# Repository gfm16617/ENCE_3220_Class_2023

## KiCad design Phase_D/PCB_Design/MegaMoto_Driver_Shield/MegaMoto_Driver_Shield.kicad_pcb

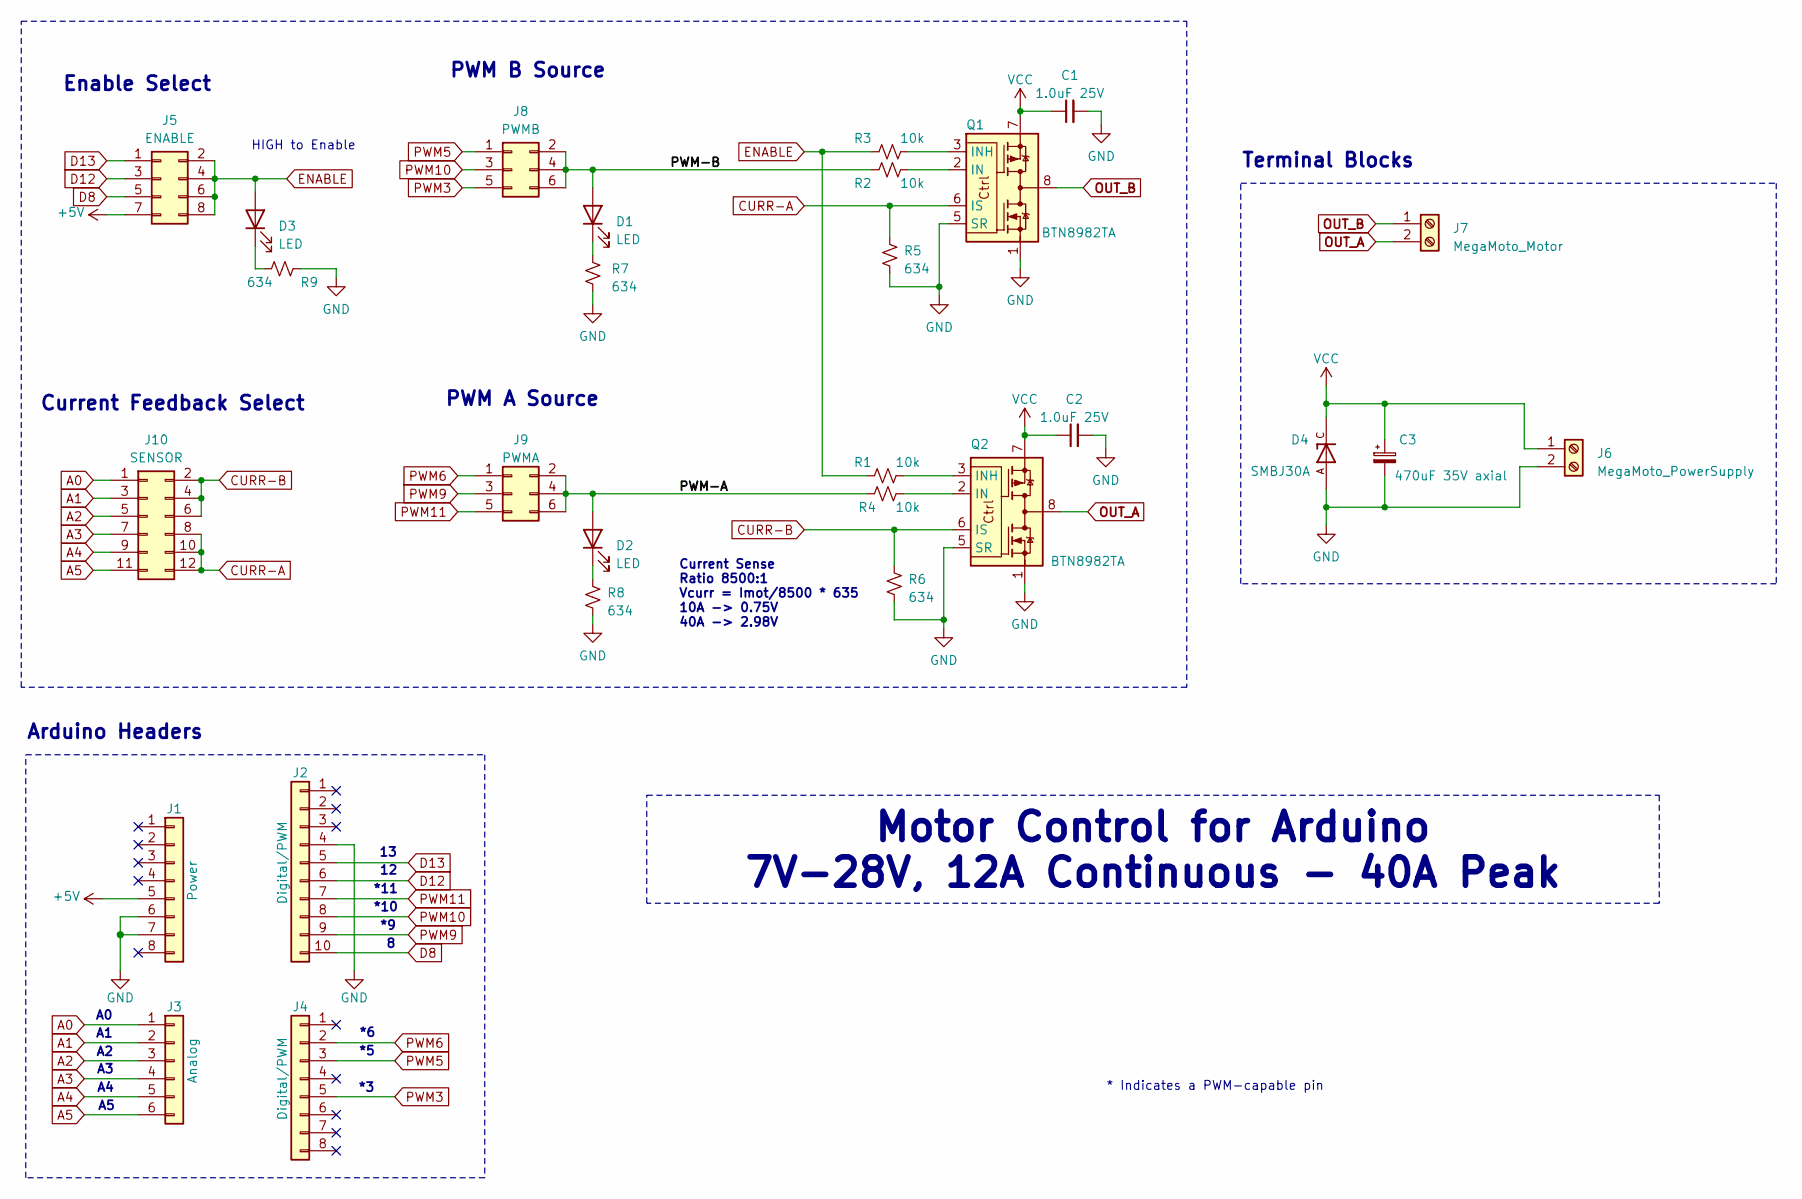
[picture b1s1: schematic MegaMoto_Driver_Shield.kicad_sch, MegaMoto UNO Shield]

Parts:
C1, C2: 1.0uF 25V; C_0603_1608Metric
C3: 470uF 35V axial; CP_Axial_L20.0mm_D10.0mm_P26.00mm_Horizontal
D1, D2, D3: LED; LED_0805_2012Metric
D4: SMBJ30A; DIOM4336X265N; PARTREV F2102
J1: Power; PinSocket_1x08_P2.54mm_Vertical
J2: Digital/PWM; PinSocket_1x10_P2.54mm_Vertical
J3: Analog; PinSocket_1x06_P2.54mm_Vertical
J4: Digital/PWM; PinSocket_1x08_P2.54mm_Vertical
J5: ENABLE; PinHeader_2x04_P2.54mm_Vertical
J6: MegaMoto_PowerSupply; Term_Block_1x2_P5mm
J7: MegaMoto_Motor; Term_Block_1x2_P5mm
J8: PWMB; PinHeader_2x03_P2.54mm_Vertical
J9: PWMA; PinHeader_2x03_P2.54mm_Vertical
J10: SENSOR; PinHeader_2x06_P2.54mm_Vertical
Q1, Q2: BTN8982TA; TO-263-7_TabPin8
R1, R2, R3, R4: 10k; R_0603_1608Metric
R5, R6, R7, R8, R9: 634; R_0603_1608Metric

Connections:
+5V: J1.5, J5.7
/PWM-A: D2.2 (A), J9.2, J9.4, J9.6, R4.1
/PWM-B: D1.2 (A), J8.2, J8.4, J8.6, R2.1
A0: J3.1, J10.1
A1: J3.2, J10.3
A2: J3.3, J10.5
A3: J3.4, J10.7
A4: J3.5, J10.9
A5: J3.6, J10.11
CURR-A: J10.8, J10.10, J10.12, Q1.6 (IS), R5.1
CURR-B: J10.2, J10.4, J10.6, Q2.6 (IS), R6.1
D8: J2.10, J5.5
D12: J2.6, J5.3
D13: J2.5, J5.1
ENABLE: D3.2 (A), J5.2, J5.4, J5.6, J5.8, R1.1, R3.1
GND: C1.2, C2.2, C3.2, D4.A, J1.6, J1.7, J2.4, J6.2, Q1.1, Q1.5 (SR), Q2.1, Q2.5 (SR), R5.2, R6.2, R7.2, R8.2, R9.2
unnamed: D1.1 (K), R7.1
unnamed: D2.1 (K), R8.1
unnamed: D3.1 (K), R9.1
unnamed: Q1.2 (IN), R2.2
unnamed: Q1.3 (INH), R3.2
unnamed: Q2.2 (IN), R4.2
unnamed: Q2.3 (INH), R1.2
OUT_A: J7.2, Q2.4, Q2.8
OUT_B: J7.1, Q1.4, Q1.8
PWM3: J4.5, J8.5
PWM5: J4.3, J8.1
PWM6: J4.2, J9.1
PWM9: J2.9, J9.3
PWM10: J2.8, J8.3
PWM11: J2.7, J9.5
VCC: C1.1, C2.1, C3.1, D4.C, J6.1, Q1.7, Q2.7

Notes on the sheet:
Motor Control for Arduino 7V-28V, 12A Continuous - 40A Peak
Terminal Blocks
Current Sense Ratio 8500:1 Vcurr = Imot/8500 * 635 10A -> 0.75V 40A -> 2.98V
*11
HIGH to Enable
Current Feedback Select
Enable Select
PWM A Source
*10
PWM B Source
* Indicates a PWM-capable pin
Arduino Headers

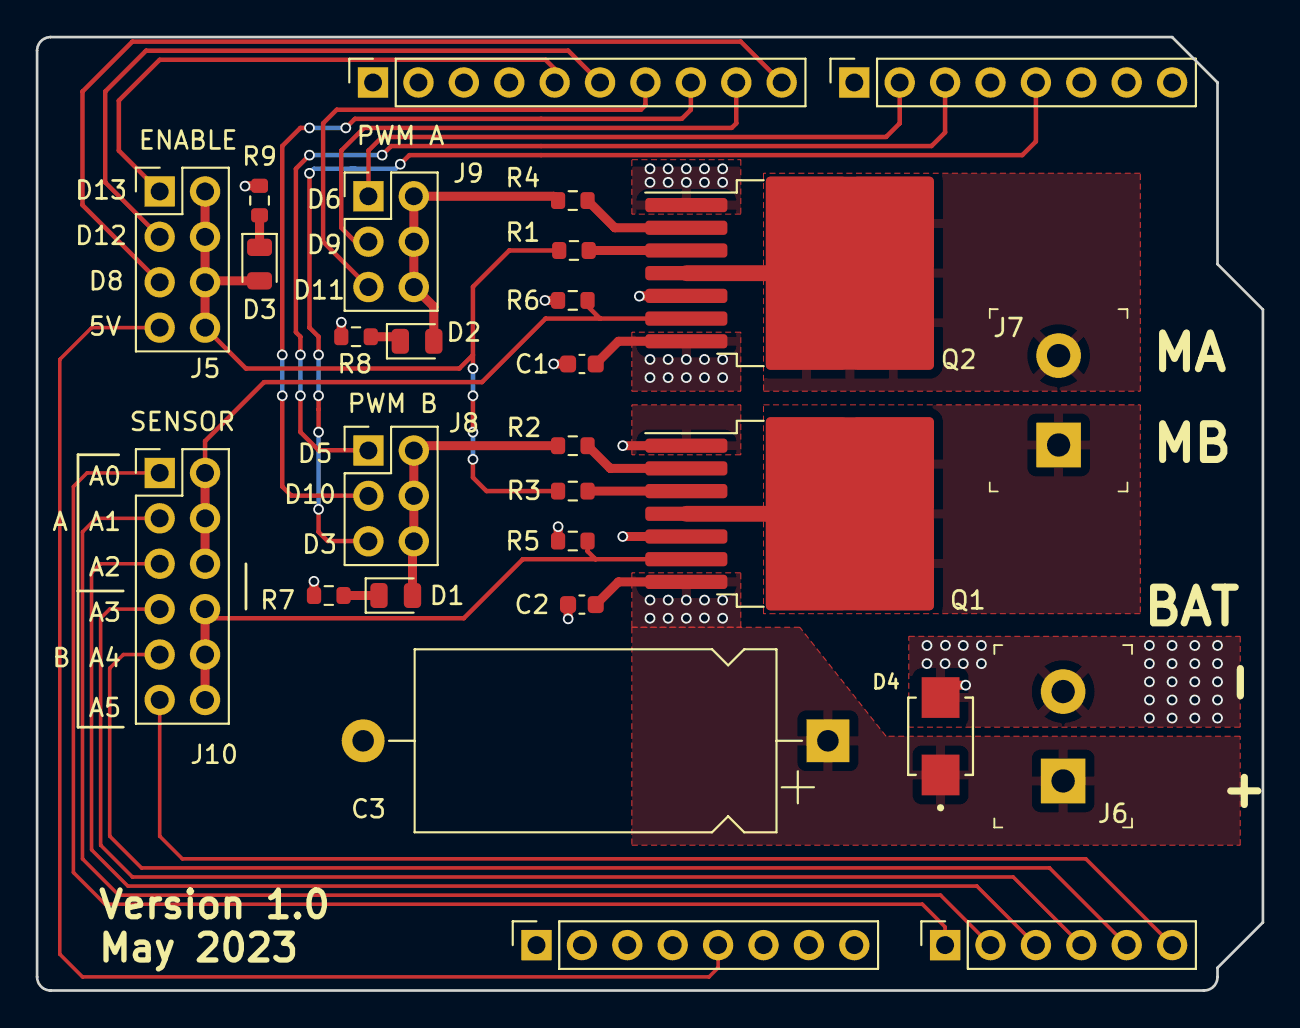
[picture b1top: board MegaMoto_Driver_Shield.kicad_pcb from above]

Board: 2 copper layers, 68.6 x 53.3 mm, 28 parts (0 on the bottom side), 32 nets.

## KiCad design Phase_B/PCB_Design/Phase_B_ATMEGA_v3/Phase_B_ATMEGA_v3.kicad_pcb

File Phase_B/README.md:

## Table of Contents
- [PCB Soldering Schedule](#pcb-soldering-schedule)

## PCB Soldering Schedule

|         | Tuesday (closed) | Wednesday (closed) | Thursday (closed) |  Friday (closed) |
|---------|:----------------:|:------------------:|:-----------------:|:----------------:|
| 4pm-6pm | Harsha K.        | Ryan Considine     |                   | Leo Gomez        |
|         | Alex Kondracki   | David Ki           |                   | Kevin Fuentes    |
|         | Jon McHorse      | Brian Lee          |                   | Bryce Swearingen |
|         | Evan Hill        | Ethan Burnett      |                   | Eric Jacobs      |
|         | Toby Werthan     | Raul Medina        |                   | Zach Bayler      |
|         | Chris Nodine     | Daniel Silva       |                   | John Leseur      |
|         |                  |                    |                   | Avery Doss       |
|         |                  |                    |                   |                  |
| 5pm-7pm |                  |                    | Madeline Bohn     |                  |
|         |                  |                    | Cole Schweizer    |                  |
|         |                  |                    | Reagan Hardy      |                  |
|         |                  |                    | Brendan Pipta     |                  |
|         |                  |                    | Noe Sheridan      |                  |
|         |                  |                    | Josh              |                  |
|         |                  |                    | Griffin Wiley     |                  |

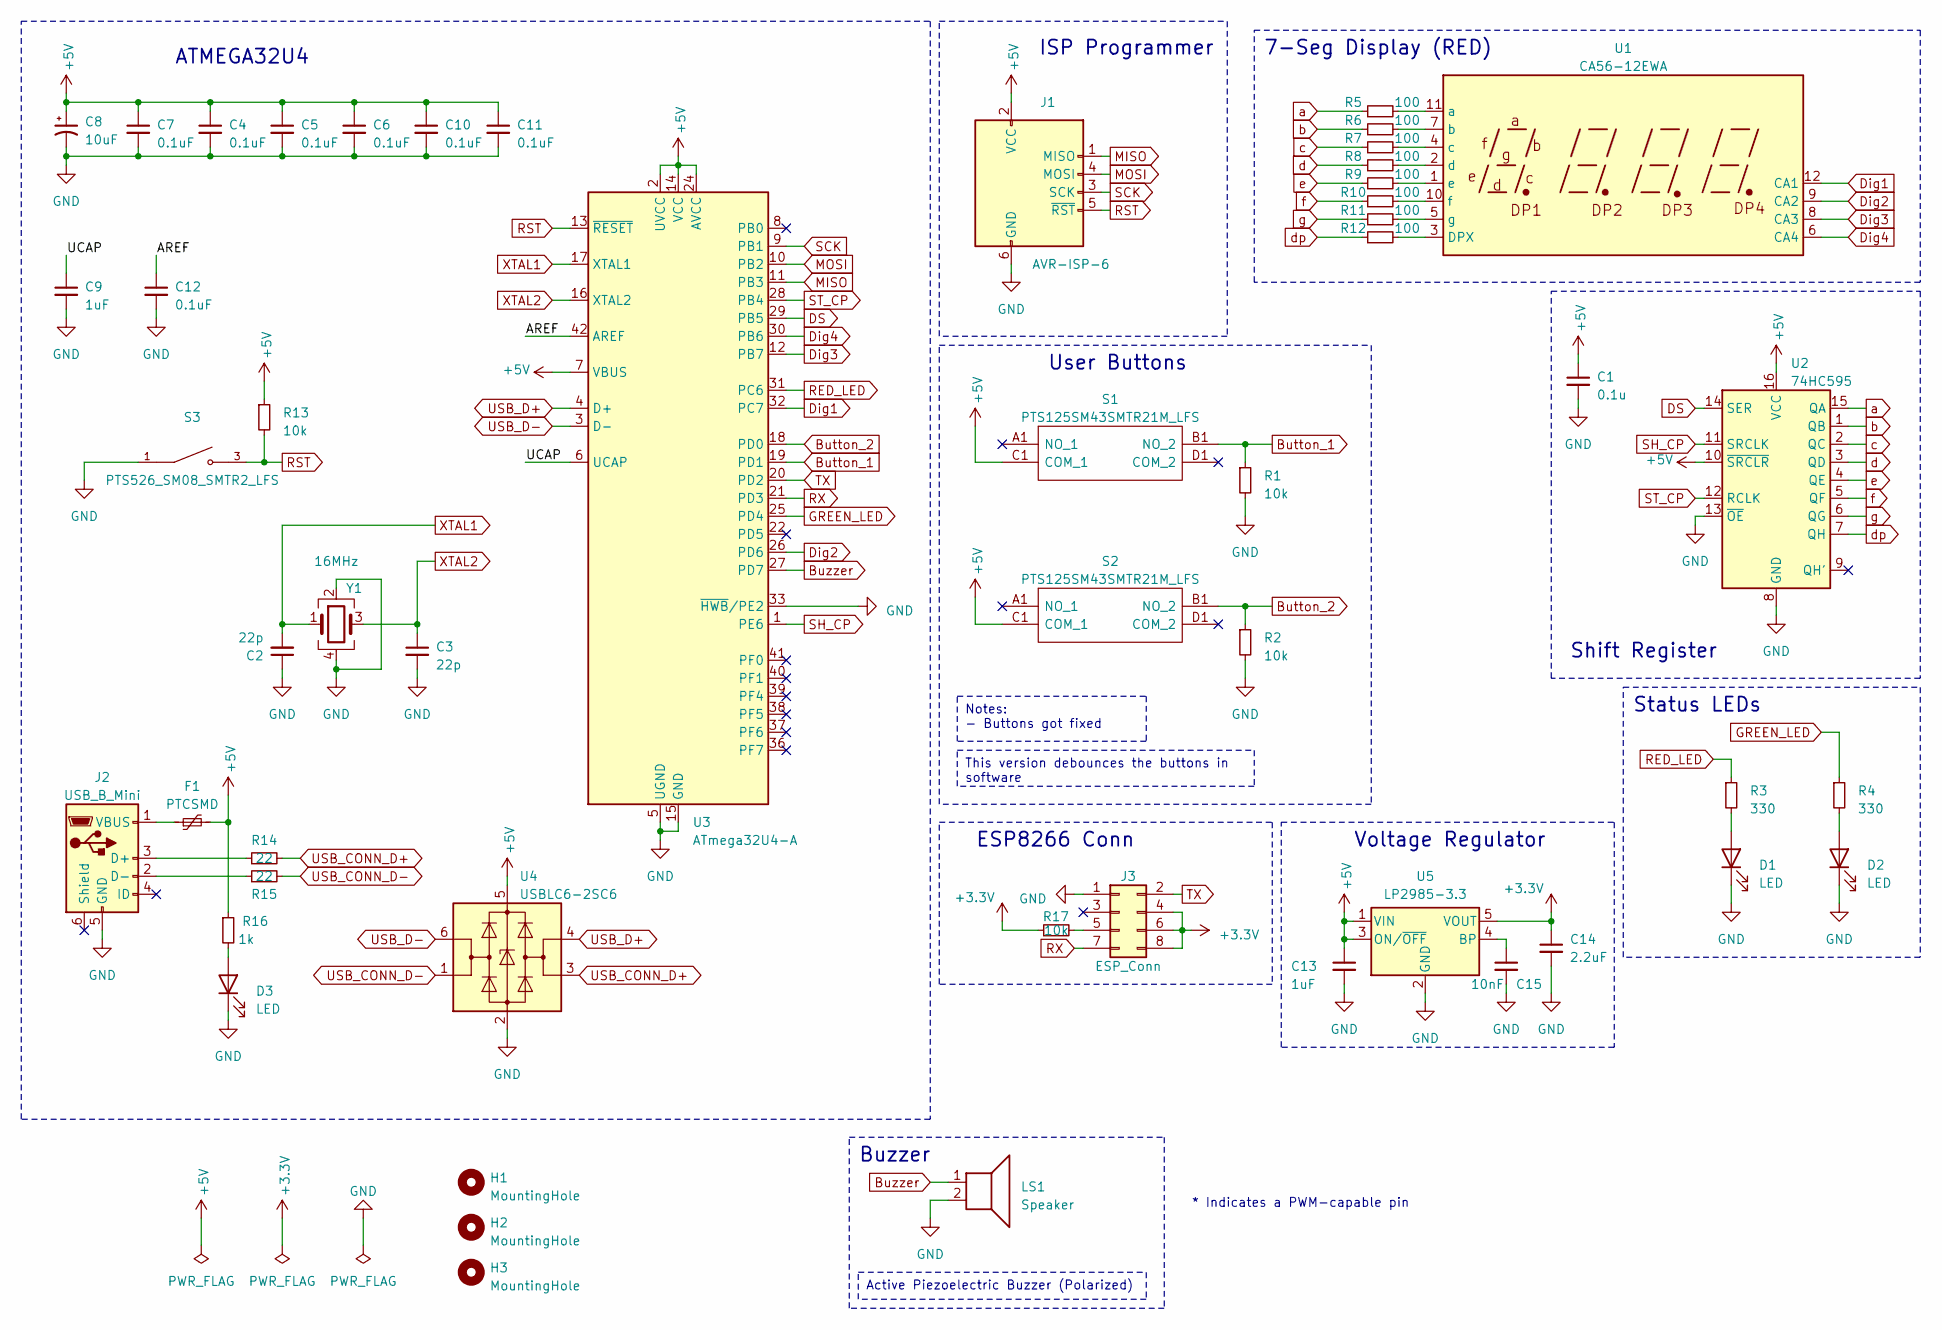
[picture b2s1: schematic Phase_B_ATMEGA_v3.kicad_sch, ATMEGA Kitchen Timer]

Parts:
C1: 0.1u; C_0603_1608Metric
C2, C3: 22p; C_0603_1608Metric
C4, C5, C6, C7, C10, C11, C12: 0.1uF; C_0603_1608Metric
C8: 10uF; C_0805_2012Metric
C9, C13: 1uF; C_0603_1608Metric
C14: 2.2uF; C_0603_1608Metric
C15: 10nF; C_0603_1608Metric
D1, D2, D3: LED; LED_0805_2012Metric
F1: PTCSMD; Fuse_1812_4532Metric
H1, H2, H3: MountingHole; MountingHole_3.2mm_M3_Pad
J1: AVR-ISP-6; PinSocket_2x03_P2.54mm_Vertical
J2: USB_B_Mini; USB_Mini-B_Lumberg_2486_01_Horizontal
J3: ESP_Conn; PinSocket_2x04_P2.54mm_Vertical
LS1: Speaker; Buzzer_12x9.5RM7.6
R1, R2: 10k; R_0805_2012Metric
R3, R4: 330; R_0805_2012Metric
R5, R6, R7, R8, R9, R10, R11, R12: 100; R_0805_2012Metric
R13, R17: 10k; R_0603_1608Metric
R14, R15: 22; R_0603_1608Metric
R16: 1k; R_0603_1608Metric
S1, S2: PTS125SM43SMTR21M_LFS; PTS125_SMD_Button; Manufacturer_Part_Number PTS125SM43SMTR21M LFS; Mouser Part Number 611-PTS125S43SMTRLFS
S3: PTS526_SM08_SMTR2_LFS; PTS526_SMD_Button; PARTREV 20 mar 19
U1: CA56-12EWA
U2: 74HC595; TSSOP-16_4.4x5mm_P0.65mm
U3: ATmega32U4-A; TQFP-44_10x10mm_P0.8mm
U4: USBLC6-2SC6; SOT-23-6
U5: LP2985-3.3; SOT-23-5
Y1: 16MHz; Crystal_SMD_Abracon_ABM8G-4Pin_3.2x2.5mm

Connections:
+3.3V: C14.1, J3.4, J3.6, J3.8, R17.1, U5.5 (VOUT)
+5V: C1.1, C4.1, C5.1, C6.1, C7.1, C8.1, C10.1, C11.1, C13.1, F1.2, J1.2 (VCC), R13.1, R16.1, S1.C1 (COM_1), S2.C1 (COM_1), U2.10 (~SRCLR), U2.16 (VCC), U3.2 (UVCC), U3.7 (VBUS), U3.14 (VCC), U3.24 (AVCC), U3.34 (VCC), U3.44 (AVCC), U4.5 (VBUS), U5.1 (VIN), U5.3 (ON/~OFF)
/AREF: C12.1, U3.42 (AREF)
/UCAP: C9.1, U3.6 (UCAP)
Button_1: R1.1, S1.B1 (NO_2), U3.19 (PD1)
Button_2: R2.1, S2.B1 (NO_2), U3.18 (PD0)
Buzzer: LS1.1, U3.27 (PD7)
DS: U2.14 (SER), U3.29 (PB5)
Dig1: U1.12 (CA1), U3.32 (PC7)
Dig2: U1.9 (CA2), U3.26 (PD6)
Dig3: U1.8 (CA3), U3.12 (PB7)
Dig4: U1.6 (CA4), U3.30 (PB6)
GND: C1.2, C2.1, C3.2, C4.2, C5.2, C6.2, C7.2, C8.2, C9.2, C10.2, C11.2, C12.2, C13.2, C14.2, C15.2, D1.1 (K), D2.1 (K), D3.1 (K), J1.6 (GND), J2.5 (GND), J3.1, LS1.2, R1.2, R2.2, S3.1, U2.8 (GND), U2.13 (~OE), U3.5 (UGND), U3.15 (GND), U3.23 (GND), U3.33 (~HWB/PE2), U3.35 (GND), U3.43 (GND), U4.2 (GND), U5.2 (GND), Y1.2, Y1.4
GREEN_LED: R4.1, U3.25 (PD4)
MISO: J1.1 (MISO), U3.11 (PB3)
MOSI: J1.4 (MOSI), U3.10 (PB2)
unnamed: D1.2 (A), R3.2
unnamed: D2.2 (A), R4.2
unnamed: D3.2 (A), R16.2
unnamed: J2.3 (D+), R14.1
unnamed: J2.2 (D-), R15.1
unnamed: F1.1, J2.1 (VBUS)
unnamed: J3.5, R17.2
unnamed: R12.2, U1.3 (DPX)
unnamed: R5.2, U1.11 (a)
unnamed: R6.2, U1.7 (b)
unnamed: R7.2, U1.4 (c)
unnamed: R8.2, U1.2 (d)
unnamed: R9.2, U1.1 (e)
unnamed: R10.2, U1.10 (f)
unnamed: R11.2, U1.5 (g)
unnamed: C15.1, U5.4 (BP)
RED_LED: R3.1, U3.31 (PC6)
RST: J1.5 (~RST), R13.2, S3.3, U3.13 (~RESET)
RX: J3.7, U3.21 (PD3)
SCK: J1.3 (SCK), U3.9 (PB1)
SH_CP: U2.11 (SRCLK), U3.1 (PE6)
ST_CP: U2.12 (RCLK), U3.28 (PB4)
TX: J3.2, U3.20 (PD2)
USB_CONN_D+: R14.2, U4.3 (I/O2)
USB_CONN_D-: R15.2, U4.1 (I/O1)
USB_D+: U3.4 (D+), U4.4 (I/O2)
USB_D-: U3.3 (D-), U4.6 (I/O1)
XTAL1: C2.2, U3.17 (XTAL1), Y1.1
XTAL2: C3.1, U3.16 (XTAL2), Y1.3
a: R5.1, U2.15 (QA)
b: R6.1, U2.1 (QB)
c: R7.1, U2.2 (QC)
d: R8.1, U2.3 (QD)
dp: R12.1, U2.7 (QH)
e: R9.1, U2.4 (QE)
f: R10.1, U2.5 (QF)
g: R11.1, U2.6 (QG)

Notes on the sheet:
Notes: - Buttons got fixed
Active Piezoelectric Buzzer (Polarized)
This version debounces the buttons in software
Shift Register
Voltage Regulator
Status LEDs
ATMEGA32U4
User Buttons
Buzzer
* Indicates a PWM-capable pin
7-Seg Display (RED)
ISP Programmer
ESP8266 Conn

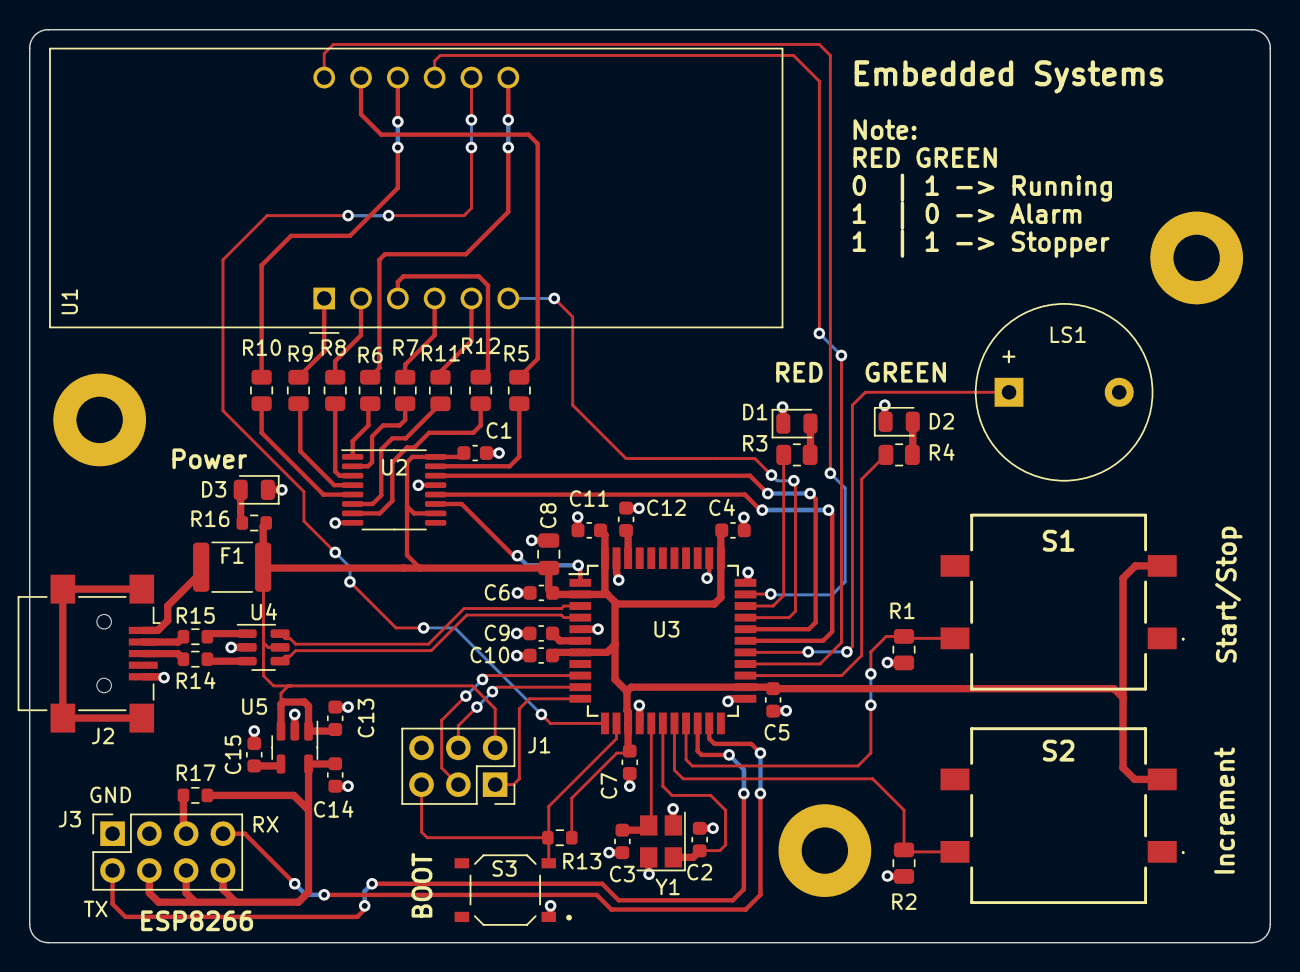
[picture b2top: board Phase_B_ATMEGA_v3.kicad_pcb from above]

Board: 2 copper layers, 85.6 x 63.0 mm, 52 parts (0 on the bottom side), 53 nets.

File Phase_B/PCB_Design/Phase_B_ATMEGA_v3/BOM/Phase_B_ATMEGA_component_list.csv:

null,Placed,References,Value,Footprint,Quantity
1,,"C1, C4, C5, C6, C7, C10, C11, C12",0.1uF,C_0603_1608Metric,8
2,,"C2, C3",22p,C_0603_1608Metric,2
3,,"C9, C13",1uF,C_0603_1608Metric,2
4,,C8,10uF,C_0805_2012Metric,1
5,,C14,2.2uF,C_0603_1608Metric,1
6,,C15,10nF,C_0603_1608Metric,1
7,,"R5, R6, R7, R8, R9, R10, R11, R12",100,R_0805_2012Metric,8
8,,"R1, R2",10k,R_0805_2012Metric,2
9,,"R3, R4",330,R_0805_2012Metric,2
10,,"R13, R17",10k,R_0603_1608Metric,2
11,,"R14, R15",22,R_0603_1608Metric,2
12,,R16,1k,R_0603_1608Metric,1
13,,"D1, D2, D3",LED,LED_0805_2012Metric,3
14,,U1,CA56-12EWA,CA56-12EWA,1
15,,U2,74HC595,TSSOP-16_4.4x5mm_P0.65mm,1
16,,U3,ATmega32U4-A,TQFP-44_10x10mm_P0.8mm,1
17,,U4,USBLC6-2SC6,SOT-23-6,1
18,,U5,LP2985-3.3,SOT-23-5,1
19,,Y1,16MHz,Crystal_SMD_Abracon_ABM8G-4Pin_3.2x2.5mm,1
20,,F1,PTCSMD,Fuse_1812_4532Metric,1
21,,"S1, S2",PTS125SM43SMTR21M_LFS,PTS125_SMD_Button,2
22,,LS1,Speaker,Buzzer_12x9.5RM7.6,1
23,,S3,PTS526_SM08_SMTR2_LFS,PTS526_SMD_Button,1
24,,J1,AVR-ISP-6,PinSocket_2x03_P2.54mm_Vertical,1
25,,J2,USB_B_Mini,USB_Mini-B_Lumberg_2486_01_Horizontal,1
26,,J3,ESP_Conn,PinSocket_2x04_P2.54mm_Vertical,1

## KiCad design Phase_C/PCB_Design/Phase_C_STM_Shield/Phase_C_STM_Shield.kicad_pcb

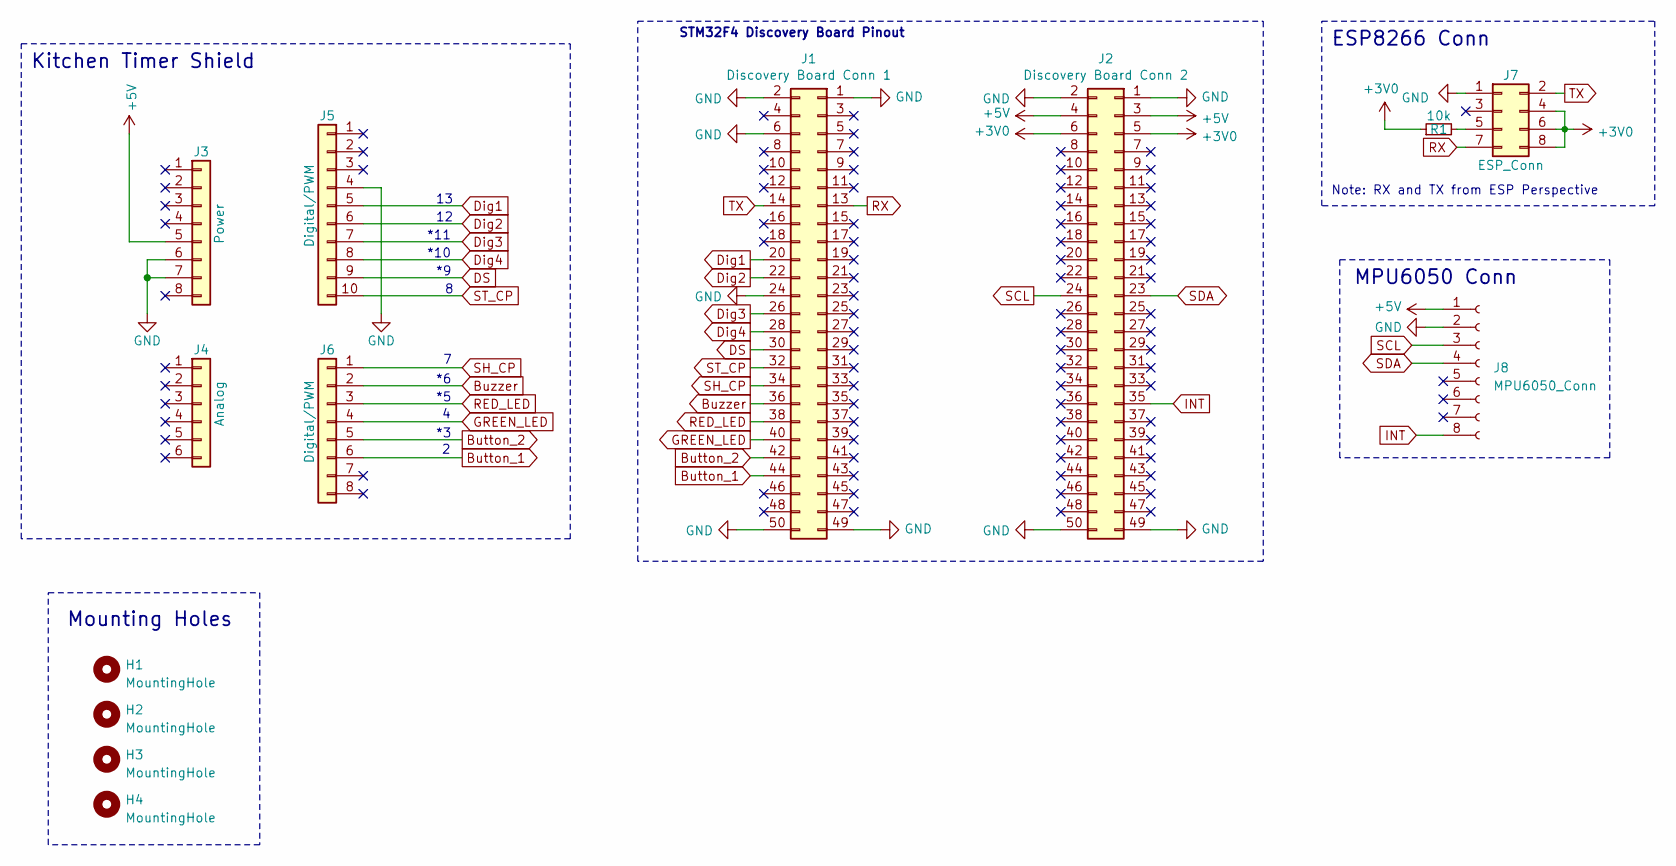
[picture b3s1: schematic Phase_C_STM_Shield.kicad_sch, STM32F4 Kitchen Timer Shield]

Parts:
H1, H2, H3, H4: MountingHole; MountingHole_3.2mm_M3_Pad
J1: Discovery Board Conn 1; PinSocket_2x25_P2.54mm_Vertical
J2: Discovery Board Conn 2; PinSocket_2x25_P2.54mm_Vertical
J3: Power; PinSocket_1x08_P2.54mm_Vertical
J4: Analog; PinSocket_1x06_P2.54mm_Vertical
J5: Digital/PWM; PinSocket_1x10_P2.54mm_Vertical
J6: Digital/PWM; PinSocket_1x08_P2.54mm_Vertical
J7: ESP_Conn; PinSocket_2x04_P2.54mm_Vertical
J8: MPU6050_Conn; PinSocket_1x08_P2.54mm_Vertical
R1: 10k; R_Axial_DIN0207_L6.3mm_D2.5mm_P10.16mm_Horizontal

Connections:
+3V0: J2.5, J2.6, J7.4, J7.6, J7.8, R1.1
+5V: J2.3, J2.4, J3.5, J8.1
Button_1: J1.44, J6.6
Button_2: J1.42, J6.5
Buzzer: J1.36, J6.2
DS: J1.30, J5.9
Dig1: J1.20, J5.5
Dig2: J1.22, J5.6
Dig3: J1.26, J5.7
Dig4: J1.28, J5.8
GND: J1.1, J1.2, J1.6, J1.24, J1.49, J1.50, J2.1, J2.2, J2.49, J2.50, J3.6, J3.7, J5.4, J7.1, J8.2
GREEN_LED: J1.40, J6.4
INT: J2.35, J8.8
unnamed: J7.5, R1.2
RED_LED: J1.38, J6.3
RX: J1.13, J7.7
SCL: J2.24, J8.3
SDA: J2.23, J8.4
SH_CP: J1.34, J6.1
ST_CP: J1.32, J5.10
TX: J1.14, J7.2

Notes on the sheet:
Note: RX and TX from ESP Perspective
MPU6050 Conn
ESP8266 Conn
*10
*11
Mounting Holes
Kitchen Timer Shield
STM32F4 Discovery Board Pinout

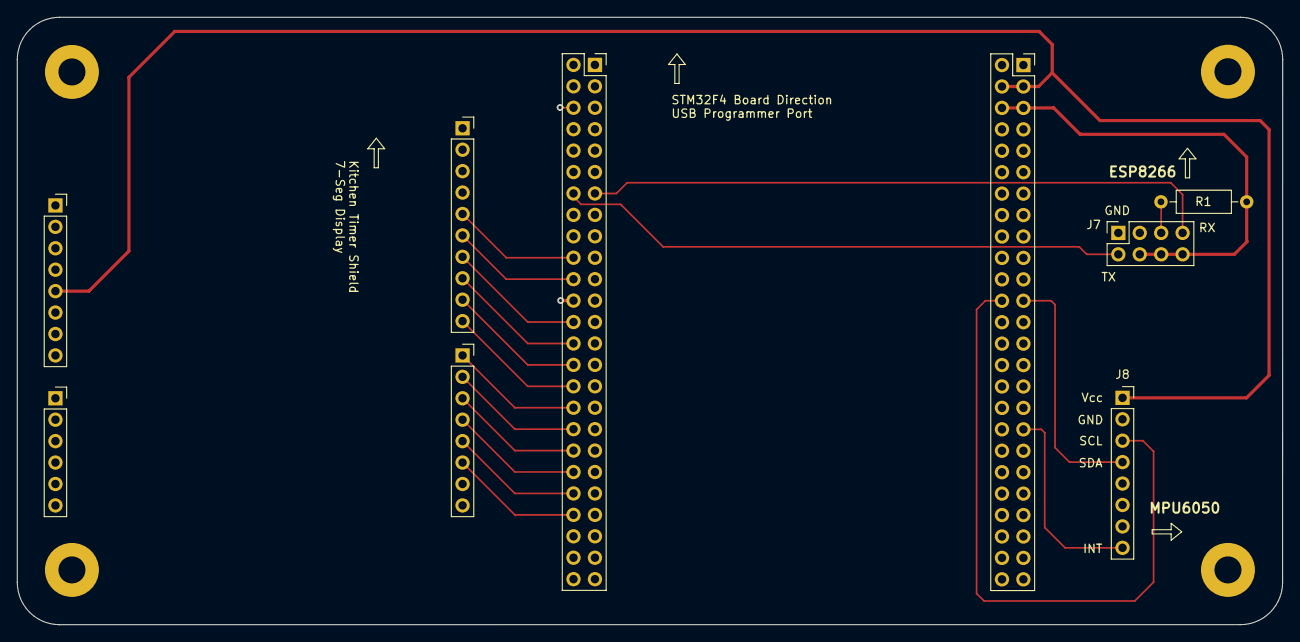
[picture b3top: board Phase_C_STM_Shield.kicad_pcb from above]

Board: 2 copper layers, 150.0 x 72.0 mm, 13 parts (0 on the bottom side), 21 nets.

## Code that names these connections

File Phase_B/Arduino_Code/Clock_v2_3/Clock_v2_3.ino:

#include <Arduino.h>
#include <avr/power.h>

#define PF0   A5
#define PF1   A4
#define PF4   A3
#define PF5   A2
#define PF6   A1
#define PF7   A0

#define DIGIT_1   13  // PC7
#define RED_LED   5   // PC6
#define DIGIT_4   10  // PB6
#define DATA      9   // PB5 -> DS
#define LATCH     8   // PB4 -> ST_CP
#define BUZZER    6   // PD7
#define DIGIT_2   12  // PD6
#define GREEN_LED 4   // PD4

#define PD5       NotMappedPort_PD5 // Not Mapped on Leonardo Board
#define PD3       1                 // TX
#define PD2       0                 // RX
#define BUTTON_1  2                 // PD1 -> Start/Stop Timer and Stop Buzzer 
#define BUTTON_2  3                 // PD0 -> Inc Timer
#define DIGIT_3   11                // PB7

#define PB3   NotMappedPort_PB3   // MISO -> Not Mapped on Leonardo Board
#define PB2   NotMappedPort_PB2   // MOSI -> Not Mapped on Leonardo Board
#define PB1   NotMappedPort_PB1   // SCK -> Not Mapped on Leonardo Board
#define PB0   NotMappedPort_PB0   // SS -> Not Mapped on Leonardo Board
#define CLOCK 7                   // PE6 -> SH_CP

// 7-Seg Display Variables
unsigned char gtable[]=
{0x3f,0x06,0x5b,0x4f,0x66,0x6d,0x7d,0x07,0x7f,0x6f,0x77,0x7c
,0x39,0x5e,0x79,0x71,0x00};
byte gCurrentDigit;

// Volatile Variables
volatile unsigned char gISRFlag1   = 0;
volatile unsigned char gBuzzerFlag = 0;

// Timer Variables
#define DEFAULT_COUNT 30     // default value is 30secs
volatile int  gCount        = DEFAULT_COUNT;
unsigned char gTimerRunning = 0; 

unsigned int gReloadTimer1 = 62499; // corresponds to 1 second
byte         gReloadTimer2 = 200;  // display refresh time

/**
 * @brief Setup peripherals and timers
 * @param
 * @return
 */
void setup() {

  if(F_CPU == 16000000) clock_prescale_set(clock_div_1);
  
  // LEDs Pins
  pinMode(RED_LED, OUTPUT);
  pinMode(GREEN_LED, OUTPUT);

  // LEDs -> Timer Stopped
  digitalWrite(RED_LED, HIGH);
  digitalWrite(GREEN_LED, HIGH);

  // Button Pins
  pinMode(BUTTON_1, INPUT_PULLUP);
  attachInterrupt(digitalPinToInterrupt(BUTTON_1), buttonISR1, RISING);
  pinMode(BUTTON_2, INPUT_PULLUP);
  attachInterrupt(digitalPinToInterrupt(BUTTON_2), buttonISR2, RISING);

  // Buzer Pins
  pinMode(BUZZER, OUTPUT);

  // Buzzer -> Off
  digitalWrite(BUZZER,LOW);

  // 7-Seg Display
  pinMode(DIGIT_1, OUTPUT);
  pinMode(DIGIT_2, OUTPUT);
  pinMode(DIGIT_3, OUTPUT);
  pinMode(DIGIT_4, OUTPUT);

  // Shift Register Pins
  pinMode(LATCH, OUTPUT);
  pinMode(CLOCK, OUTPUT);
  pinMode(DATA, OUTPUT);

  dispOff();  // turn off the display

  // Initialize Timer1 (16bit) -> Used for clock
  // OCR1A = (F_CPU / (N * f_target)) - 1
  // Speed of Timer1 = (16e6 / (256 * 1)) - 1 = 62499
  noInterrupts();
  TCCR1A = 0;
  TCCR1B = 0;
  OCR1A = gReloadTimer1; // compare match register 16MHz/256
  TCCR1B |= (1<<WGM12);   // CTC mode
  // Start Timer by setting the prescaler -> done using the start button
  //TCCR1B |= (1<<CS12);    // 256 prescaler 
  TIMSK1 |= (1<<OCIE1A);  // enable timer compare interrupt
  interrupts();

  // Initialize Timer3 (16bit) -> Used to refresh display
  // Speed of Timer3 = 16MHz/64 = 250 KHz
  TCCR3A = 0;
  TCCR3B = 0;
  OCR3A = gReloadTimer2;            // max value 2^16 - 1 = 65535
  TCCR3A |= (1<<WGM31);
  TCCR3B = (1<<CS31) | (1<<CS30);   // 64 prescaler
  TIMSK3 |= (1<<OCIE3A);
  interrupts();                     // enable all interrupts
}

/**
 * @brief Shifts the bits through the shift register
 * @param num
 * @param dp
 * @return
 */
void display(unsigned char num, unsigned char dp)
{
  digitalWrite(LATCH, LOW);
  shiftOut(DATA, CLOCK, MSBFIRST, gtable[num] | (dp<<7));
  digitalWrite(LATCH, HIGH);
}

/**
 * @brief Turns the 7-seg display off
 * @param
 * @return
 */
void dispOff()
{
   digitalWrite(DIGIT_1, HIGH);
   digitalWrite(DIGIT_2, HIGH);
   digitalWrite(DIGIT_3, HIGH);
   digitalWrite(DIGIT_4, HIGH);
}

/**
 * @brief Button 2 ISR
 * @param
 * @return
 */
void buttonISR2()
{
  // Increment Clock
  gCount++;
}

/**
 * @brief Button 1 ISR
 * @param
 * @return
 */
void buttonISR1()
{ 
  // Set ISR Flag
  gISRFlag1 = 1;
}

/**
 * @brief Timer 2 ISR
 * @param TIMER2_COMPA_vect
 * @return
 */
ISR(TIMER3_COMPA_vect)   // Timer2 interrupt service routine (ISR)
{
  dispOff();  // turn off the display
 
  switch (gCurrentDigit)
  {
    case 1: //0x:xx
      display( int((gCount/60) / 10) % 6, 0 );   // prepare to display digit 1 (most left)
      digitalWrite(DIGIT_1, LOW);  // turn on digit 1
      break;
 
    case 2: //x0:xx
      display( int(gCount / 60) % 10, 1 );   // prepare to display digit 2
      digitalWrite(DIGIT_2, LOW);     // turn on digit 2
      break;
 
    case 3: //xx:0x
      display( (gCount / 10) % 6, 0 );   // prepare to display digit 3
      digitalWrite(DIGIT_3, LOW);    // turn on digit 3
      break;
 
    case 4: //xx:x0
      display(gCount % 10, 0); // prepare to display digit 4 (most right)
      digitalWrite(DIGIT_4, LOW);  // turn on digit 4
      break;

    default:
      break;
  }
 
  gCurrentDigit = (gCurrentDigit % 4) + 1;
}

/**
 * @brief Timer 1 ISR
 * @param TIMER1_COMPA_vect
 * @return
 */
ISR(TIMER1_COMPA_vect)  // Timer1 interrupt service routine (ISR)
{
  gCount--;

  if(gCount == 0)
  {
      // Stop Timer
      stopTimer1();
      
      // Raise Alarm
      gBuzzerFlag = 1;
      gTimerRunning = 0;
  }
}

/**
 * @brief Stop Timer 1
 * @param
 * @return
 */
void stopTimer1()
{
  // Stop Timer
  TCCR1B &= 0b11111000; // stop clock
  TIMSK1 = 0; // cancel clock timer interrupt
}

/**
 * @brief Start Timer 1
 * @param
 * @return
 */
void startTimer1()
{
  // Start Timer
  TCCR1B |= (1<<CS12);    // 256 prescaler
  TIMSK1 |= (1<<OCIE1A);  // enable timer compare interrupt
}

/**
 * @brief Turn On Buzzer
 * @param
 * @return
 */
void activeBuzzer()
{
  unsigned char i;
  unsigned char sleepTime = 1; // ms
  
  for(i=0;i<100;i++)
  {
    digitalWrite(BUZZER,HIGH);
    delay(sleepTime);//wait for 1ms
    digitalWrite(BUZZER,LOW);
    delay(sleepTime);//wait for 1ms
  }
}

/**
 * @brief Main Loop
 * @param
 * @return
 */
void loop() 
{
  // Attend Button 2 ISR
  if(gISRFlag1 == 1)
  {
    // Reset ISR Flag
    gISRFlag1 = 0;

    if(gTimerRunning == 0)
    {
      // Start Timer
      gTimerRunning = 1;

      if(gCount == 0)
        gCount = DEFAULT_COUNT;

      if(gBuzzerFlag == 1)
      {
        gBuzzerFlag = 0;

        // LEDs -> Timer Stopped
        digitalWrite(RED_LED, HIGH);
        digitalWrite(GREEN_LED, HIGH);
      }
      else
      {
        startTimer1();
        // LEDs -> Timer Running
        digitalWrite(RED_LED, LOW);
        digitalWrite(GREEN_LED, HIGH);
      }
    }
    else
    {
      // Stop Timer
      stopTimer1();
      gTimerRunning = 0;

      // LEDs -> Timer Running
      digitalWrite(RED_LED, HIGH);
      digitalWrite(GREEN_LED, HIGH);
    }
  }

  // Attend gBuzzerFlag
  if(gBuzzerFlag == 1)
  {
    // Make Noise...
    digitalWrite(RED_LED, HIGH);
    digitalWrite(GREEN_LED, LOW);
    activeBuzzer();
  }
}

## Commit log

2023-04-07 ENCE 3220 Template Structure
2023-04-13 Phase B PCB Design files
2023-04-13 Phase B Notes added
2023-04-13 more photos
2023-04-13 file name fixed
2023-04-13 new files addded
2023-04-13 files added
2023-04-15 PCB Power test
2023-04-15 ISP Connector Mistake and Fix
2023-04-15 Blink LED Test
2023-04-15 PCB Buttons Fixed
2023-04-15 New Files for v3 PCB
2023-04-15 PCB Esp v3 gif
2023-04-15 Phase B Atmega v3
2023-04-15 removed old pic
2023-04-15 new pics
2023-04-15 removed old design
2023-04-15 new project
2023-04-16 code updated
2023-04-16 more code added
2023-04-16 freertos
2023-04-16 remove old project
2023-04-16 new project added
2023-04-16 files removed
2023-04-16 enclosure files added to the project
2023-04-17 phase b folder removed
2023-05-11 Notes Folder for Phase C
2023-05-11 PCB Design Shield for Phase C
2023-05-11 Template Code
2023-05-11 Phase B enclosure
2023-05-11 Notes folder Phase B
2023-05-11 Arduino code folder Phase B
2023-05-11 PCB design Phase B
2023-05-11 deleted
2023-05-11 template for phase c
2023-05-22 readme file
2023-05-24 Phase D documentation
2023-06-09 new code
2023-06-09 esp code
2023-06-09 code with freertos
2023-06-09 code without comms
